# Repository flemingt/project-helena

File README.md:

# project-helena
Atari XL keyboard replacement

What can go wrong with a bunch of switches? :)

Building on Ivop's project I've designed rev B, C, & D of the board.
Rev D has been designed with slightly different ribbon cable mounting points and moved the LED solder location to shorten the length of the board by a few mm. It is now ~111x346mm

The Helena Aux pcb plugs into the keyboard ribbon slot on the mainboard. For the 600XL 0.8mm seems to work, but 0.6mm or thinner is required for the 800XL.

I've added holes to make the switches PCB mount, some holes to mount stabilisers for the spacebar, and even more holes to align with the metal backplane of the original mylar / Stackpole keyboard of my 600XL. Maybe someone will need the mounting holes in the future. 

I've designed some 3D printed bracketry to use the screw posts in the top half of the case. Also some upper supports to minimise keyboard flex. These hook on to the PCB and the aluminium pieces that hold the cartridge doors.

I've designed cherry to Stackpole replacement stems for mechanical switches, but in the end I went for adaptors.

In addition, I've created a bracket to mount the U1MB expansion board. Note, you'll have to relocate the battery to make this all fit in the confines of a 600XL.

All the 3D printed parts use standard PLA, 50% infill. Some of the shapes area a bit tricky, but I've successfully printed everything with some thought on orientation and supports in the slicer.

Scorpio_NY on the Atariage forums has created 3D printable plates which will stiffen up the keyboard PCB and allow more accurate mounting on the switches. See the "Plate Files" directory. To accomodate the plates he's also developed new stabilizer files (in the "Final Stab Files" directory) and support brackets (in the "Final Support Bracket Files" directory).

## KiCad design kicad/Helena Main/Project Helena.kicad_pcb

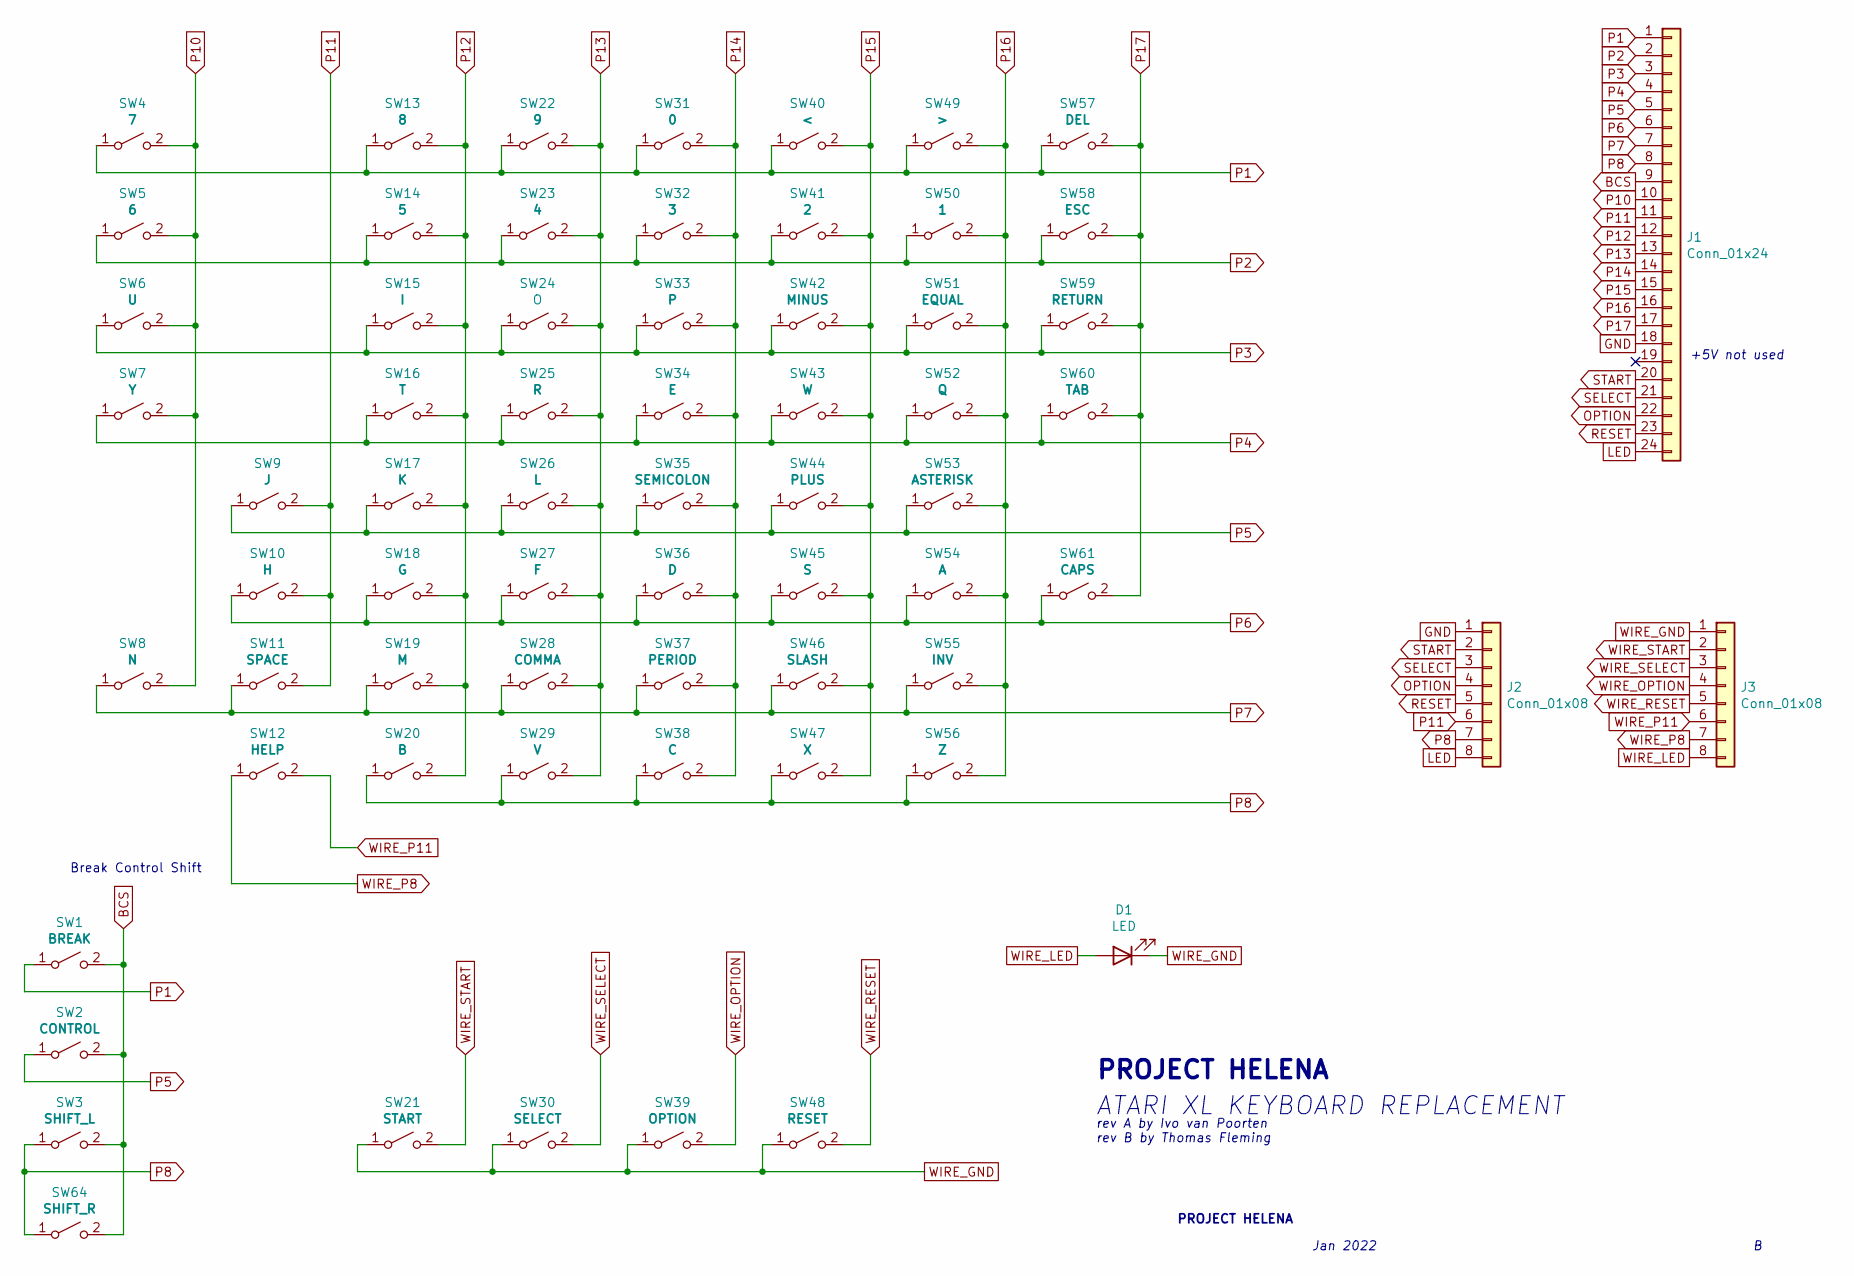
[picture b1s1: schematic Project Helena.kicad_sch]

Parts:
D1: LED; LED_D5.0mm
J1: Conn_01x24; PinHeader_1x24_P2.54mm_Vertical
J2, J3: Conn_01x08; PinHeader_1x08_P2.54mm_Vertical
SW1: BREAK; SW_Cherry_MX1A_1.00u_Plate
SW2: CONTROL; SW_Cherry_MX1A_2.00u_Plate
SW3: SHIFT_L; SW_Cherry_MX1A_1.50u_Plate
SW4: 7; SW_Cherry_MX1A_1.00u_Plate
SW5: 6; SW_Cherry_MX1A_1.00u_Plate
SW6: U; SW_Cherry_MX1A_1.00u_Plate
SW7: Y; SW_Cherry_MX1A_1.00u_Plate
SW8: N; SW_Cherry_MX1A_1.00u_Plate
SW9: J; SW_Cherry_MX1A_1.00u_Plate
SW10: H; SW_Cherry_MX1A_1.00u_Plate
SW11: SPACE; SW_Cherry_MX1A_1.00u_Plate
SW12: HELP; SW_Cherry_MX1A_1.00u_Plate
SW13: 8; SW_Cherry_MX1A_1.00u_Plate
SW14: 5; SW_Cherry_MX1A_1.00u_Plate
SW15: I; SW_Cherry_MX1A_1.00u_Plate
SW16: T; SW_Cherry_MX1A_1.00u_Plate
SW17: K; SW_Cherry_MX1A_1.00u_Plate
SW18: G; SW_Cherry_MX1A_1.00u_Plate
SW19: M; SW_Cherry_MX1A_1.00u_Plate
SW20: B; SW_Cherry_MX1A_1.00u_Plate
SW21: START; SW_Cherry_MX1A_1.00u_Plate
SW22: 9; SW_Cherry_MX1A_1.00u_Plate
SW23: 4; SW_Cherry_MX1A_1.00u_Plate
SW24: O; SW_Cherry_MX1A_1.00u_Plate
SW25: R; SW_Cherry_MX1A_1.00u_Plate
SW26: L; SW_Cherry_MX1A_1.00u_Plate
SW27: F; SW_Cherry_MX1A_1.00u_Plate
SW28: COMMA; SW_Cherry_MX1A_1.00u_Plate
SW29: V; SW_Cherry_MX1A_1.00u_Plate
SW30: SELECT; SW_Cherry_MX1A_1.00u_Plate
SW31: 0; SW_Cherry_MX1A_1.00u_Plate
SW32: 3; SW_Cherry_MX1A_1.00u_Plate
SW33: P; SW_Cherry_MX1A_1.00u_Plate
SW34: E; SW_Cherry_MX1A_1.00u_Plate
SW35: SEMICOLON; SW_Cherry_MX1A_1.00u_Plate
SW36: D; SW_Cherry_MX1A_1.00u_Plate
SW37: PERIOD; SW_Cherry_MX1A_1.00u_Plate
SW38: C; SW_Cherry_MX1A_1.00u_Plate
SW39: OPTION; SW_Cherry_MX1A_1.00u_Plate
SW40: <; SW_Cherry_MX1A_1.00u_Plate
SW41: 2; SW_Cherry_MX1A_1.00u_Plate
SW42: MINUS; SW_Cherry_MX1A_1.00u_Plate
SW43: W; SW_Cherry_MX1A_1.00u_Plate
SW44: PLUS; SW_Cherry_MX1A_1.00u_Plate
SW45: S; SW_Cherry_MX1A_1.00u_Plate
SW46: SLASH; SW_Cherry_MX1A_1.00u_Plate
SW47: X; SW_Cherry_MX1A_1.00u_Plate
SW48: RESET; SW_Cherry_MX1A_1.00u_Plate
SW49: >; SW_Cherry_MX1A_1.00u_Plate
SW50: 1; SW_Cherry_MX1A_1.00u_Plate
SW51: EQUAL; SW_Cherry_MX1A_1.00u_Plate
SW52: Q; SW_Cherry_MX1A_1.00u_Plate
SW53: ASTERISK; SW_Cherry_MX1A_1.00u_Plate
SW54: A; SW_Cherry_MX1A_1.00u_Plate
SW55: INV; SW_Cherry_MX1A_1.00u_Plate
SW56: Z; SW_Cherry_MX1A_1.00u_Plate
SW57: DEL; SW_Cherry_MX1A_1.00u_Plate
SW58: ESC; SW_Cherry_MX1A_1.25u_Plate
SW59: RETURN; SW_Cherry_MX1A_1.50u_Plate
SW60: TAB; SW_Cherry_MX1A_1.75u_Plate
SW61: CAPS; SW_Cherry_MX1A_1.25u_Plate
SW64: SHIFT_R; SW_Cherry_MX1A_1.75u_Plate

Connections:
BCS: J1.9, SW1.2 (B), SW2.2 (B), SW3.2 (B), SW64.2 (B)
GND: J1.18, J2.1
LED: J1.24, J2.8
OPTION: J1.22, J2.4
P1: J1.1, SW1.1 (A), SW4.1 (A), SW13.1 (A), SW22.1 (A), SW31.1 (A), SW40.1 (A), SW49.1 (A), SW57.1 (A)
P2: J1.2, SW5.1 (A), SW14.1 (A), SW23.1 (A), SW32.1 (A), SW41.1 (A), SW50.1 (A), SW58.1 (A)
P3: J1.3, SW6.1 (A), SW15.1 (A), SW24.1 (A), SW33.1 (A), SW42.1 (A), SW51.1 (A), SW59.1 (A)
P4: J1.4, SW7.1 (A), SW16.1 (A), SW25.1 (A), SW34.1 (A), SW43.1 (A), SW52.1 (A), SW60.1 (A)
P5: J1.5, SW2.1 (A), SW9.1 (A), SW17.1 (A), SW26.1 (A), SW35.1 (A), SW44.1 (A), SW53.1 (A)
P6: J1.6, SW10.1 (A), SW18.1 (A), SW27.1 (A), SW36.1 (A), SW45.1 (A), SW54.1 (A), SW61.1 (A)
P7: J1.7, SW8.1 (A), SW11.1 (A), SW19.1 (A), SW28.1 (A), SW37.1 (A), SW46.1 (A), SW55.1 (A)
P8: J1.8, J2.7, SW3.1 (A), SW20.1 (A), SW29.1 (A), SW38.1 (A), SW47.1 (A), SW56.1 (A), SW64.1 (A)
P10: J1.10, SW4.2 (B), SW5.2 (B), SW6.2 (B), SW7.2 (B), SW8.2 (B)
P11: J1.11, J2.6, SW9.2 (B), SW10.2 (B), SW11.2 (B)
P12: J1.12, SW13.2 (B), SW14.2 (B), SW15.2 (B), SW16.2 (B), SW17.2 (B), SW18.2 (B), SW19.2 (B), SW20.2 (B)
P13: J1.13, SW22.2 (B), SW23.2 (B), SW24.2 (B), SW25.2 (B), SW26.2 (B), SW27.2 (B), SW28.2 (B), SW29.2 (B)
P14: J1.14, SW31.2 (B), SW32.2 (B), SW33.2 (B), SW34.2 (B), SW35.2 (B), SW36.2 (B), SW37.2 (B), SW38.2 (B)
P15: J1.15, SW40.2 (B), SW41.2 (B), SW42.2 (B), SW43.2 (B), SW44.2 (B), SW45.2 (B), SW46.2 (B), SW47.2 (B)
P16: J1.16, SW49.2 (B), SW50.2 (B), SW51.2 (B), SW52.2 (B), SW53.2 (B), SW54.2 (B), SW55.2 (B), SW56.2 (B)
P17: J1.17, SW57.2 (B), SW58.2 (B), SW59.2 (B), SW60.2 (B), SW61.2 (B)
RESET: J1.23, J2.5
SELECT: J1.21, J2.3
START: J1.20, J2.2
WIRE_GND: D1.1 (K), J3.1, SW21.1 (A), SW30.1 (A), SW39.1 (A), SW48.1 (A)
WIRE_LED: D1.2 (A), J3.8
WIRE_OPTION: J3.4, SW39.2 (B)
WIRE_P8: J3.7, SW12.1 (A)
WIRE_P11: J3.6, SW12.2 (B)
WIRE_RESET: J3.5, SW48.2 (B)
WIRE_SELECT: J3.3, SW30.2 (B)
WIRE_START: J3.2, SW21.2 (B)

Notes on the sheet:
+5V not used
Break Control Shift
rev A by Ivo van Poorten rev B by Thomas Fleming
ATARI XL KEYBOARD REPLACEMENT
Jan 2022
PROJECT HELENA

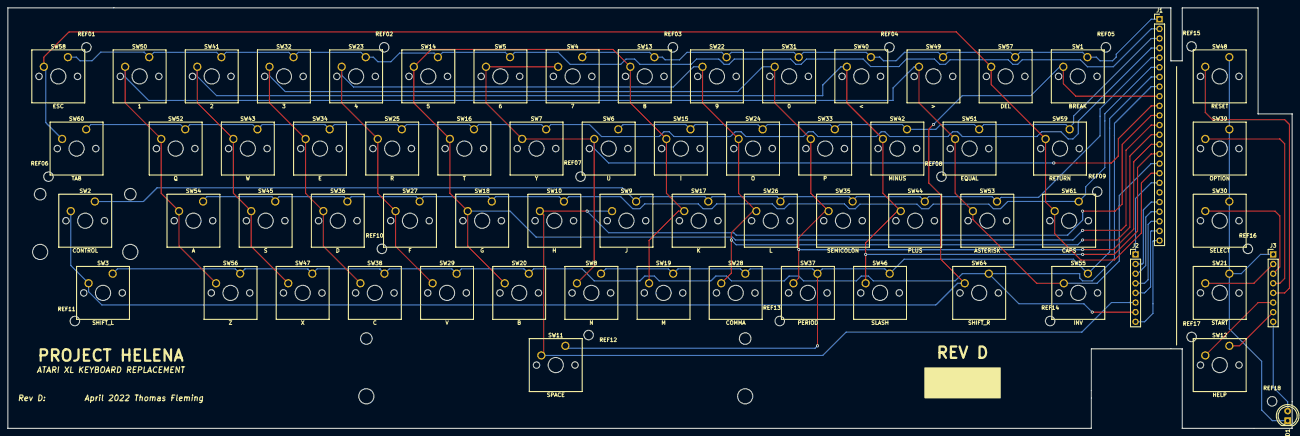
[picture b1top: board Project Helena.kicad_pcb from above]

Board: 2 copper layers, 339.0 x 111.0 mm, 84 parts (0 on the bottom side), 31 nets.

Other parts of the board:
REF01, REF02, REF03, REF04, REF05, REF06, REF07, REF08, REF09, REF10, REF11, REF12, REF13, REF14, REF15, REF16, REF17, REF18: MountingHole_2.5mm

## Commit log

2022-01-27 Created Rev B
    Rev B of ivops Atari600xl keyboard.
    Modified switch footprints to accommodate 5 holes for stability.
    Added PCB mount stabilizer holes for 3D printed brackets.
    Added through-holes to match the metal backplate on my membrane 600xl keyboard with the intention of making stand-offs.
    Extensively rerouted traces to avoid all the new holes.
2022-01-27 Update README.md
    changed image to rev B design
2022-01-28 adding 3D printing file/folder
    adding folder for 3D printing and rev 1 of cherry to stackpole stem replacement
2022-01-28 Update README.md
    Adding detail around rev 2.
    Added to do list.
2022-02-01 cherry / Gateron to stackpole replacement stem v2
    Version 2 with longer Stackpole section to accommodate keypress full travel
2022-02-02 cherry / Gateron to stackpole replacement stem v3
    Redrew CAD from scratch and added some stabilising features
2022-02-05 Add files via upload
    raised wings by 0.75mm and narrowed each by 0.5mm
2022-03-18 Add files via upload
    Updated PCB to rev C. Moved backplane holes for better alignment. Moved main connector to prevent ribbon cable overlap with daughterboard.
2022-03-19 Update README.md
    updated to reflect current status of rev C
2022-03-20 Delete cherry to stackpole replacement stem v2.stl
    Version 4 is better
2022-03-20 Delete cherry to stackpole replacement stem v3.stl
    Version 4 is better
2022-03-20 Delete cherry to stackpole replacement stem.stl
    Version 4 is better
2022-03-20 Left hand side keyboard PCB mount
2022-04-03 Delete LHS keyboard mount V2.stl
    replacing with near final version
2022-04-03 Add files via upload
    near final keyboard mounting brackets. Z may need some tweaking
2022-04-03 Add files via upload
    Ultimate 1MB holder designed to go under the new keyboard. Note desolder and relocate the battery.
2022-04-03 Update README.md
    updating to reflect current status.
2022-04-11 Adding near final versions of 3D printable files
2022-04-22 Delete kicad directory
    preparing for rev D
2022-04-22 Add files via upload
    Updating main PCB to rev D: shorter with better placement of power LED.
    Creating rev A of Aux PCB to interface with the existing mylar connector.
2022-04-22 Delete Other resources directory
    no longer required
2022-04-22 Add files via upload
    updating main picture
2022-04-22 Update README.md
    updating main picture
2022-04-22 Add files via upload
    adding visual explainer of 3DP files
2022-04-22 Update README.md
    adding embed of 3DP explainer
2022-06-17 Retrying Gerber uploads of rev D
2022-06-17 Add files via upload
    added zip file for ease of fabrication
2022-06-17 adding zip file for convenience
2022-07-04 Add files via upload
    Widening screw holes for 800xl.
    Adding extra slot for option key PCB fitment.
2022-12-29 Add files via upload
    Scorpio_NY files
